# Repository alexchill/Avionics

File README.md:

# Avionics Code for RC Plane STEM Project FRSH

TBS

## Required Arduino Libraries

- USB Shield 2.0
- NRF

## Maintainers

- Alex Hill @alexchill

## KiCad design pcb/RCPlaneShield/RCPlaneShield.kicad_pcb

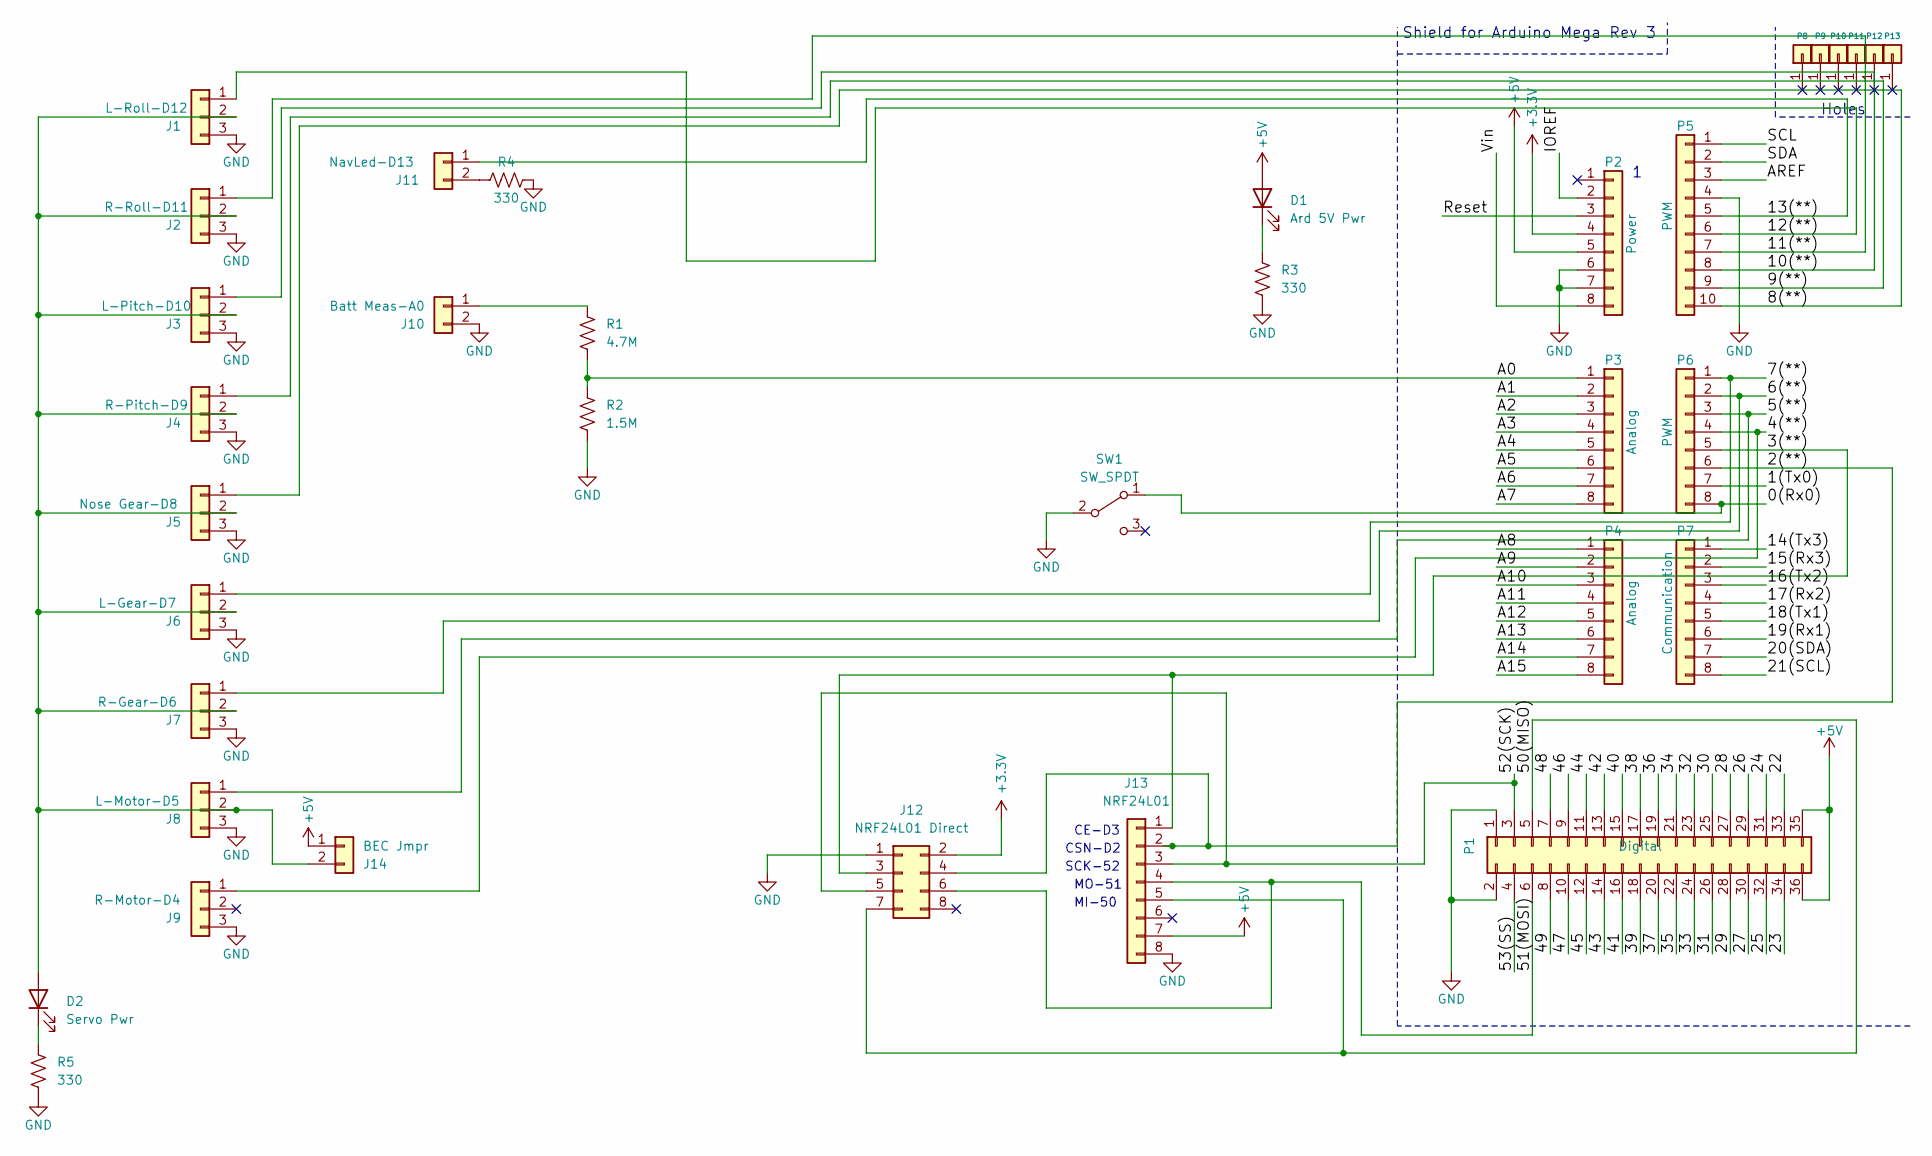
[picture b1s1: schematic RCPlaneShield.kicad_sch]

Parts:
D1: Ard 5V Pwr; LED_D5.0mm
D2: Servo Pwr; LED_D5.0mm
J1: L-Roll-D12; PinHeader_1x03_P2.54mm_Horizontal
J2: R-Roll-D11; PinHeader_1x03_P2.54mm_Horizontal
J3: L-Pitch-D10; PinHeader_1x03_P2.54mm_Horizontal
J4: R-Pitch-D9; PinHeader_1x03_P2.54mm_Horizontal
J5: Nose Gear-D8; PinHeader_1x03_P2.54mm_Horizontal
J6: L-Gear-D7; PinHeader_1x03_P2.54mm_Horizontal
J7: R-Gear-D6; PinHeader_1x03_P2.54mm_Horizontal
J8: L-Motor-D5; PinHeader_1x03_P2.54mm_Horizontal
J9: R-Motor-D4; PinHeader_1x03_P2.54mm_Horizontal
J10: Batt Meas-A0; PinHeader_1x02_P2.54mm_Vertical
J11: NavLed-D13; PinHeader_1x02_P2.54mm_Vertical
J12: NRF24L01 Direct; PinSocket_2x04_P2.54mm_Vertical
J13: NRF24L01; PinHeader_1x08_P2.54mm_Vertical
J14: BEC Jmpr; PinHeader_1x02_P2.54mm_Vertical
P1: Digital; Socket_Strip_Arduino_2x18
P2: Power; Socket_Strip_Arduino_1x08
P3, P4: Analog; Socket_Strip_Arduino_1x08
P5: PWM; Socket_Strip_Arduino_1x10
P6: PWM; Socket_Strip_Arduino_1x08
P7: Communication; Socket_Strip_Arduino_1x08
P8, P9, P10, P11, P12, P13: CONN_01X01; Arduino_1pin
R1: 4.7M; R_Axial_DIN0309_L9.0mm_D3.2mm_P12.70mm_Horizontal
R2: 1.5M; R_Axial_DIN0309_L9.0mm_D3.2mm_P12.70mm_Horizontal
R3, R4, R5: 330; R_Axial_DIN0309_L9.0mm_D3.2mm_P12.70mm_Horizontal
SW1: SW_SPDT; SW_Slide_1P2T_CK_OS102011MS2Q

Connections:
+3V3: J12.2, P2.4
+5V: D1.2 (A), J13.7, J14.1, P1.35, P1.36, P2.5
/0(Rx0): P6.8, SW1.1 (A)
/1(Tx0): P6.7
/2(**): J12.4, J13.2, P6.6
/3(**): J12.3, J13.1, P6.5
/4(**): J9.1, P6.4
/5(**): J8.1, P6.3
/6(**): J7.1, P6.2
/7(**): J6.1, P6.1
/8(**): J5.1, P5.10
/9(**): J4.1, P5.9
/10(**): J3.1, P5.8
/11(**): J2.1, P5.7
/12(**): J1.1, P5.6
/13(**): J11.1, P5.5
/14(Tx3): P7.1
/15(Rx3): P7.2
/16(Tx2): P7.3
/17(Rx2): P7.4
/18(Tx1): P7.5
/19(Rx1): P7.6
/20(SDA): P7.7
/21(SCL): P7.8
/22: P1.33
/23: P1.34
/24: P1.31
/25: P1.32
/26: P1.29
/27: P1.30
/28: P1.27
/29: P1.28
/30: P1.25
/31: P1.26
/32: P1.23
/33: P1.24
/34: P1.21
/35: P1.22
/36: P1.19
/37: P1.20
/38: P1.17
/39: P1.18
/40: P1.15
/41: P1.16
/42: P1.13
/43: P1.14
/44: P1.11
/45: P1.12
/46: P1.9
/47: P1.10
/48: P1.7
/49: P1.8
/50(MISO): J12.7, J13.5, P1.5
/51(MOSI): J12.6, J13.4, P1.6
/52(SCK): J12.5, J13.3, P1.3
/53(SS): P1.4
/A0: P3.1, R1.2, R2.1
/A1: P3.2
/A2: P3.3
/A3: P3.4
/A4: P3.5
/A5: P3.6
/A6: P3.7
/A7: P3.8
/A8: P4.1
/A9: P4.2
/A10: P4.3
/A11: P4.4
/A12: P4.5
/A13: P4.6
/A14: P4.7
/A15: P4.8
/AREF: P5.3
/IOREF: P2.2
/Reset: P2.3
/SCL: P5.1
/SDA: P5.2
/Vin: P2.8
GND: J1.3, J2.3, J3.3, J4.3, J5.3, J6.3, J7.3, J8.3, J9.3, J10.2, J12.1, J13.8, P1.1, P1.2, P2.6, P2.7, P5.4, R2.2, R3.2, R4.2, R5.2, SW1.2 (B)
unnamed: D1.1 (K), R3.1
unnamed: D2.1 (K), R5.1
unnamed: J10.1, R1.1
unnamed: J11.2, R4.1
unnamed: D2.2 (A), J1.2, J2.2, J3.2, J4.2, J5.2, J6.2, J7.2, J8.2, J14.2

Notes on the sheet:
MO-51
MI-50
Holes
SCK-52
CE-D3
CSN-D2
Shield for Arduino Mega Rev 3

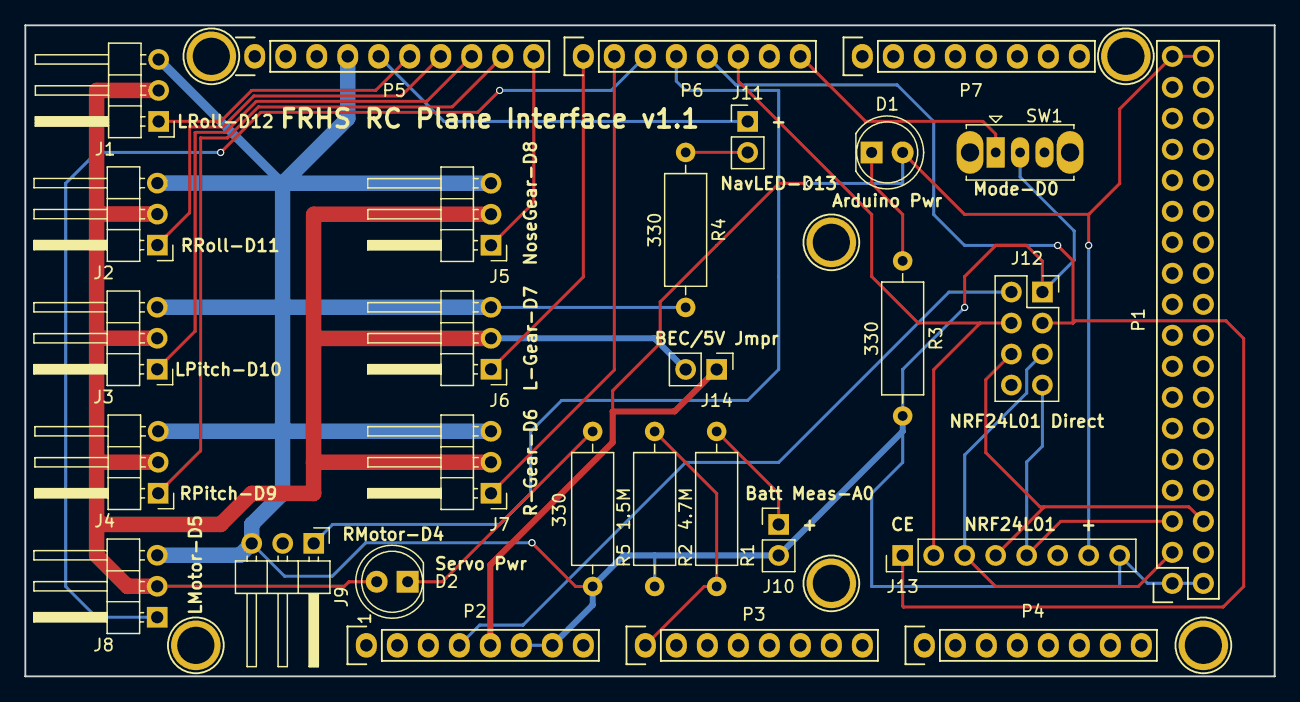
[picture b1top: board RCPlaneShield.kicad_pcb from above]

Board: 2 copper layers, 102.4 x 53.3 mm, 35 parts (0 on the bottom side), 25 nets.

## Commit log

2022-02-07 add pitch inc/dec
2022-02-21 begin add support for reading commands in serial
2022-02-21 Add BatteryMonitor and README
2022-02-21 commit xbox controller and joystick tests
2022-02-21 add sketch for uno ground
2022-02-21 convert commands to struct
2022-02-22 testing command return from and send to function
2022-02-22 set up Arduino extension for VSCode
2022-02-25 simple serial monitor app
2022-02-26 add servo test and move battery monitor
2022-02-27 add motor test
2022-02-27 Radio test
2022-02-28 change radio pins for usb shield
2022-02-28 basic transmit and receive of joystick data
2022-03-07 working servos and motor plus safety shutdown
2022-03-10 Add code to lite up navled
2022-03-30 working battery monitor with 3s Lipo
2022-03-30 set radio power to max
2022-04-09 add kicad pcb project files
2022-04-09 integrate battery measurement into plane avionics
2022-04-17 Updated digital pins used for roll, pitch, yaw
2022-04-17 Updated batt meas resistor values and servo pin numbers for PCB
2022-04-17 Refactor directory structure and names of folders
2022-04-17 Update to README to add NRF lib
2022-04-18 Update telemetry app to use anchor and allow port to be selected
2022-04-20 Move servos faster
2022-04-20 update pins for radio and fixed battery measure code
2022-04-20 send message every 4 seconds so plane knows ground is still talking
2022-04-22 Update pcb to v1.1 - wider servo traces, BEC drives servos
2022-04-22 Add printCommand function, changed motor pin to 5
2022-04-22 Missed last save to pcb file
2022-05-03 updated servo landing gear
2022-05-05 Updated ce/csn pins for new uno/mega pinout
2022-05-05 Use ack payload to send back telemetry data
2022-05-05 updated battery voltage string to look for in serial output
2022-05-05 Experiments on using ack payload
2022-05-05 Add signal strength to telemetry data
